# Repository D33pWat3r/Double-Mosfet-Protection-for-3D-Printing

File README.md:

# Double-Mosfet-Protection-for-3D-Printing

For my Anet A8 I will change to a 24V / 600W Power Supply to heating my hotbed and hotend faster.
The mainboard of a Anet A8 will not handle 24V and I must seperate the power to a extern circuit.

With a normal hotbed (1,3 Ohm) with a 24V system the current will rise drastically (ca. 18A).
Due to the high currents, the resistance of the transistors should be chosen as low as possible.

On Github you can find the circuit diagrams of the Anet A8 / A6 and typical mosfet protection boards from Aliexpress.
* [Anet 3D Board - Hardware Reverse Engineering Projekt on Github ](https://github.com/ralf-e/ANET-3D-Board-V1.0)

## Mainboard of Anet
[Mainboard](https://chinadrucker.de/wp-content/uploads/2017/07/072917_1833_ListederErs7.png)

On the normal mainboard of the Anet A8 there are IRLR7843PbF mosfets to manage the power of hotbed and hotend.
This onboard mosfet has a resistance of ~3mOhm and a thermalresistor of 1,05K/W. This mosfet can handle a lot of power. But if I change my System to 24V and more, than I must handle a current over 20A. The Thermalresistor of the onboard mosfet is not the best and the heatsink for the mosfet are not trustable.

* [Datasheet of IRLR7843PbF](https://www.infineon.com/dgdl/irlr7843pbf.pdf?fileId=5546d462533600a40153566de53526d8)

I will take the connectors for hotbed and hotend on the mainboard, which can switch my extern double mosfet board. I change the connectors of the mainbord to JST-XH connectors, because no high currents flow over it anymore.

## Extern Mosfet Protection Boards
[Example protection Board on Aliexpress](https://de.aliexpress.com/item/3D-Printer-Parts-Heated-Bed-Power-Module-Board-25A-MOSFET-For-Chitu-Motherboard/32814486198.html)

This boards has mosfets of the typ HA210N06 or YMP200N08Q which have a resistance of 3mOhm and a thermalresistance of 0,75. 

Instead, I take the mosfets of type IRF1404 because this Mosfets are cheap and have with a resistance of 4mOhm a litte bit more but a better thermalresistance.
Perhaps a take the better IRFB7430 Mosfet with some better values.
Furthermore get every power line (hotbed and hotend) 2 Mosfet. So I have some of redundancy and the half of resistance.

The main reason for a own and "better" extern mosfet board is the bad switching process by a voltage divider with two 10k resistors. This prozess needs time, where the RDs_on is chaning to high and low and produce heat. This is the reason for this ridiculous big heatsinks. Furthermore the mosfets have the best RDS_on by 10V and a voltage divider takes only the half of power voltage.

For easy plug, high-current XT60 Plugins are installed. This Connectors can handle 50A over a long time and have low connector resistance.
For the cables I take AWG 12-10 silicone cable with 3,3mm² - 5,2mm². The cable thickness is probably too much, but better too much than too low ;)

* [Datasheet of HA210N06](http://www.cecb2b.com/batchupload/inventoryother/zfa_ic_inventory/201495/zfa__332199_f13c9a0a038c37904c57614f101672ad.PDF)
* [Datasheet of YMP200N08Q](http://www.2150692.ru/files/ymp200n08q.pdf)
* [Datasheet of IRF1404](http://www.irf.com/product-info/datasheets/data/irf1404.pdf)
* [Datasheet of IRFB7430](https://github.com/D33pWat3r/Double-Mosfet-Protection-for-3D-Printing/blob/master/datasheets/datasheet_irfb7430pbf.pdf)

# References
- [Reference to https://3dprinterwiki.info/](https://3dprinterwiki.info/heatbed-terminal-burning-fix-with-mosfet-board/)

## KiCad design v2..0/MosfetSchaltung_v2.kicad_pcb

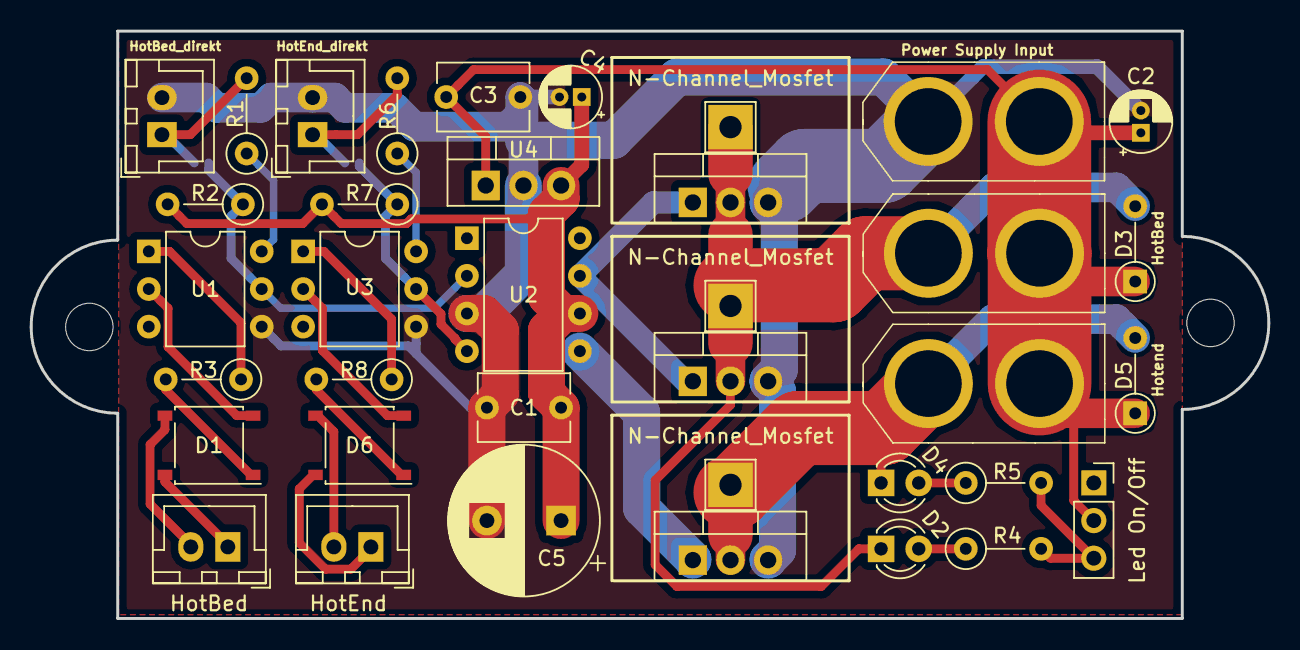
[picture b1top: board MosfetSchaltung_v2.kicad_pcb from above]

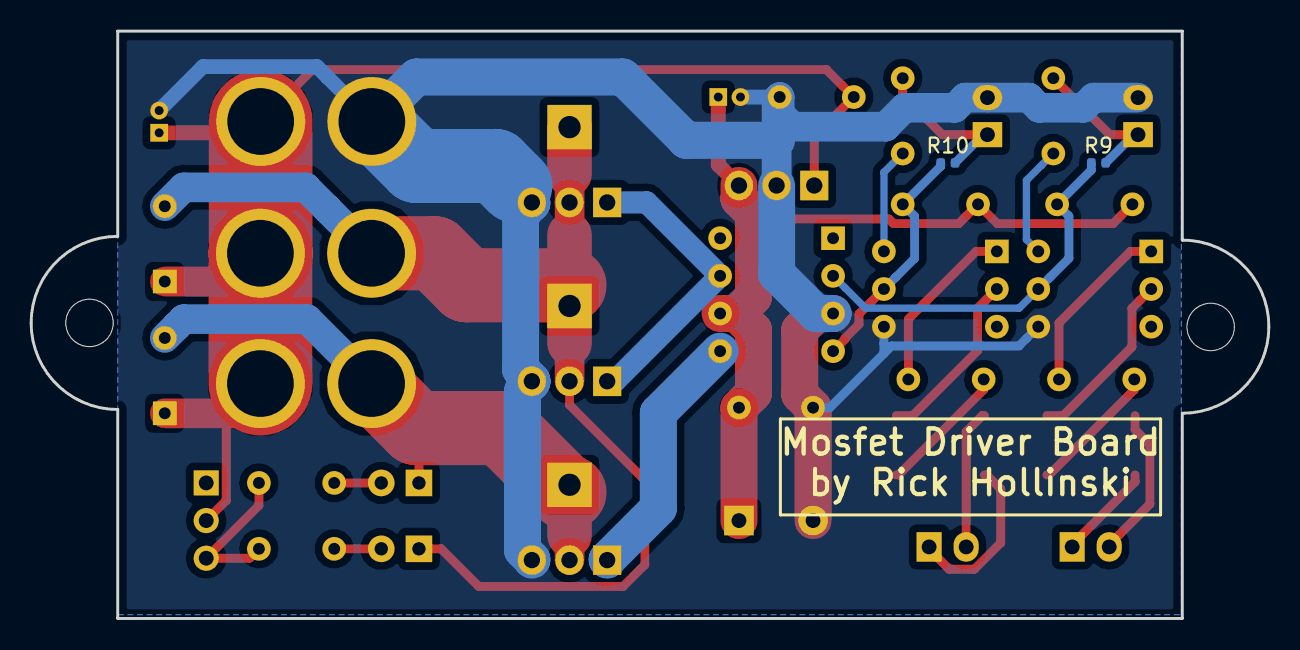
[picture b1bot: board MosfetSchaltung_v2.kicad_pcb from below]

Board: 2 copper layers, 83.5 x 39.6 mm, 41 parts (4 on the bottom side), 26 nets.

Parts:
C1, C3: 100n; C_Disc_D6.0mm_W4.4mm_P5.00mm
C2: 4,7µ; CP_Radial_D4.0mm_P1.50mm
C4: 47µ; CP_Radial_D4.0mm_P1.50mm
C5: 1000µ; CP_Radial_D10.0mm_P5.00mm
D1, D6: D_Bridge_+-AA; Diode_Bridge_Diotec_ABS
D2, D4: LED; LED_D3.0mm
D3, D5: D_Schottky; D_DO-35_SOD27_P5.08mm_Vertical_AnodeUp
J1: Power Supply Input; XT60
J2: HotBed; JST_XH_B02B-XH-A_1x02_P2.50mm_Vertical
J3: HotBed; XT60
J4: Hotend; XT60
J5: HotEnd; JST_XH_B02B-XH-A_1x02_P2.50mm_Vertical
J6: HotBed_direkt; JST_XH_B02B-XH-A_1x02_P2.50mm_Vertical
J7: HotEnd_direkt; JST_XH_B02B-XH-A_1x02_P2.50mm_Vertical
MH1, MH2: MountingHole; MountingHole_3.2mm_M3
Q1, Q2, Q3: N-Channel_Mosfet; TO-220-3_Vertical
R1, R6: 512; R_Axial_DIN0207_L6.3mm_D2.5mm_P5.08mm_Vertical
R2, R3, R7, R8: 10k; R_Axial_DIN0207_L6.3mm_D2.5mm_P5.08mm_Vertical
R4, R5: 2,2k; R_Axial_DIN0207_L6.3mm_D2.5mm_P5.08mm_Vertical
R9, R10: 0; R_0402_1005Metric
SW1: Led On/Off; PinSocket_1x03_P2.54mm_Vertical
TP1, TP2, TP3: TestPoint; TestPoint_THTPad_3.0x3.0mm_Drill1.5mm
U1, U3: 4N35; DIP-6_W7.62mm
U2: TC4426CPA; DIP-8_W7.62mm
U4: L7810; TO-220-3_Vertical

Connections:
+10V: C1.1, C4.1, C5.1, R2.2, R7.2, U2.6, U4.3
GND: C1.2, C2.2, C3.2, C4.2, C5.2, J1.1, J6.2, J7.2, Q1.3, Q2.3, Q3.3, U1.4, U2.3, U3.4, U4.2
unnamed: D1.1, R3.2
unnamed: D1.2, U1.2
unnamed: D1.3, J2.2
unnamed: D1.4, J2.1
unnamed: D2.1, D3.2, J3.1, Q1.2, Q2.2, TP1.1, TP2.1
unnamed: D2.2, R4.1
unnamed: D4.1, D5.2, J4.1, Q3.2, TP3.1
unnamed: D4.2, R5.1
unnamed: D6.1, R8.2
unnamed: D6.2, U3.2
unnamed: D6.3, J5.2
unnamed: D6.4, J5.1
unnamed: Q1.1, Q2.1, U2.7
unnamed: Q3.1, U2.5
unnamed: R1.1, U1.6
unnamed: R2.1, R9.1, U1.5, U2.2
unnamed: R3.1, U1.1
unnamed: R4.2, R5.2, SW1.3
unnamed: R6.1, U3.6
unnamed: R8.1, U3.1
unnamed: R7.1, R10.1, U2.4, U3.5
VCC: C2.1, C3.1, D3.1, D5.1, J1.2, J3.2, J4.2, SW1.2, U4.1
direct_Input1: J6.1, R1.2, R9.2
direct_Input2: J7.1, R6.2, R10.2

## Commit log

2018-01-03 Readme
2018-01-03 first Version of my Protection Board
2018-01-04 new Readme
2018-01-04 Calculation of Powerloss and heatings
2018-01-04 Calculation of Powerloss and heatings as pdf
2018-01-04 Datasheets for Mosfets
2018-01-04 XT60 Lib for Kicad
2018-01-04 corrected a mistake with the LED circuit
2018-01-04 mark the 12V row
2018-01-04 delet pcb File
2018-01-05 my gitIgnore
2018-01-05 mark the 12V line
2018-02-02 change Gate Voltage to under 15V
2018-02-10 new design for 10-35V power supplies
2018-02-10 change gitignore
2018-03-30 separate datasheets
2018-03-30 first version with a volatge divider
2018-03-30 version with transistors for mosfet bank
2018-03-30 version with an inverted dual MosfetDriver
2018-03-30 new folder struckture
2018-03-30 plot the new schemas to pdf
2018-05-18 add 2 flyback diodes; move status leds to output; add direct input connectors
2018-05-18 expand table to 36V and add a new Mosfet type
2018-05-18 change some values
2018-05-18 change description for this project
2018-12-10 Gerber Files
2018-12-10 KiCad Cicuits Files
2018-12-10 pictures of the circuit board
2018-12-11 clear files
